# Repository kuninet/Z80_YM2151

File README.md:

# Z80マイコン FM音源(YM2151)ボード (KZ80-YM2151)

- SBC8080バスにつながるFM音源ボード KZ80-YM2151 のデータ類です。
- 詳しい説明は以下のwikiを参照してください。
  - https://github.com/kuninet/Z80_YM2151/wiki

## 回路図

[PDF版の回路図はこちら](img/YM2151.pdf)

## 部品表

- 部品表は以下にあります。
  - [https://github.com/kuninet/Z80_YM2151/blob/master/KiCAD/YM2151.ods](https://github.com/kuninet/Z80_YM2151/blob/master/KiCAD/YM2151.ods)

## 演奏プログラム&サンプルデータ

- Z80用演奏プログラムとサンプルデータはsample_musicディレクトリにあります。
  - サンプル音楽は参考リンクの音楽データをもとに作成させていただきました。
- 起動方法
  1. sample_music/hexFilesの以下のインテルHex形式ファイルを機械語モニタ等でロード
      - KZ80_YM2151.hex  (8100h番地〜)
      - sample_m.hex    (9000h番地〜)
  2. 8100番地から実行してください。

## 注意点

- 接続方法が複数あり、ジャンパ設定が複雑です。[wiki](https://github.com/kuninet/Z80_YM2151/wiki)をご覧ください。

## ライセンス

- 本リポジトリのデータは MIT License のもとで公開します。

## 参考リンク
- github h1romas4/arduino-vgmplayer
  - https://github.com/h1romas4/arduino-vgmplayer

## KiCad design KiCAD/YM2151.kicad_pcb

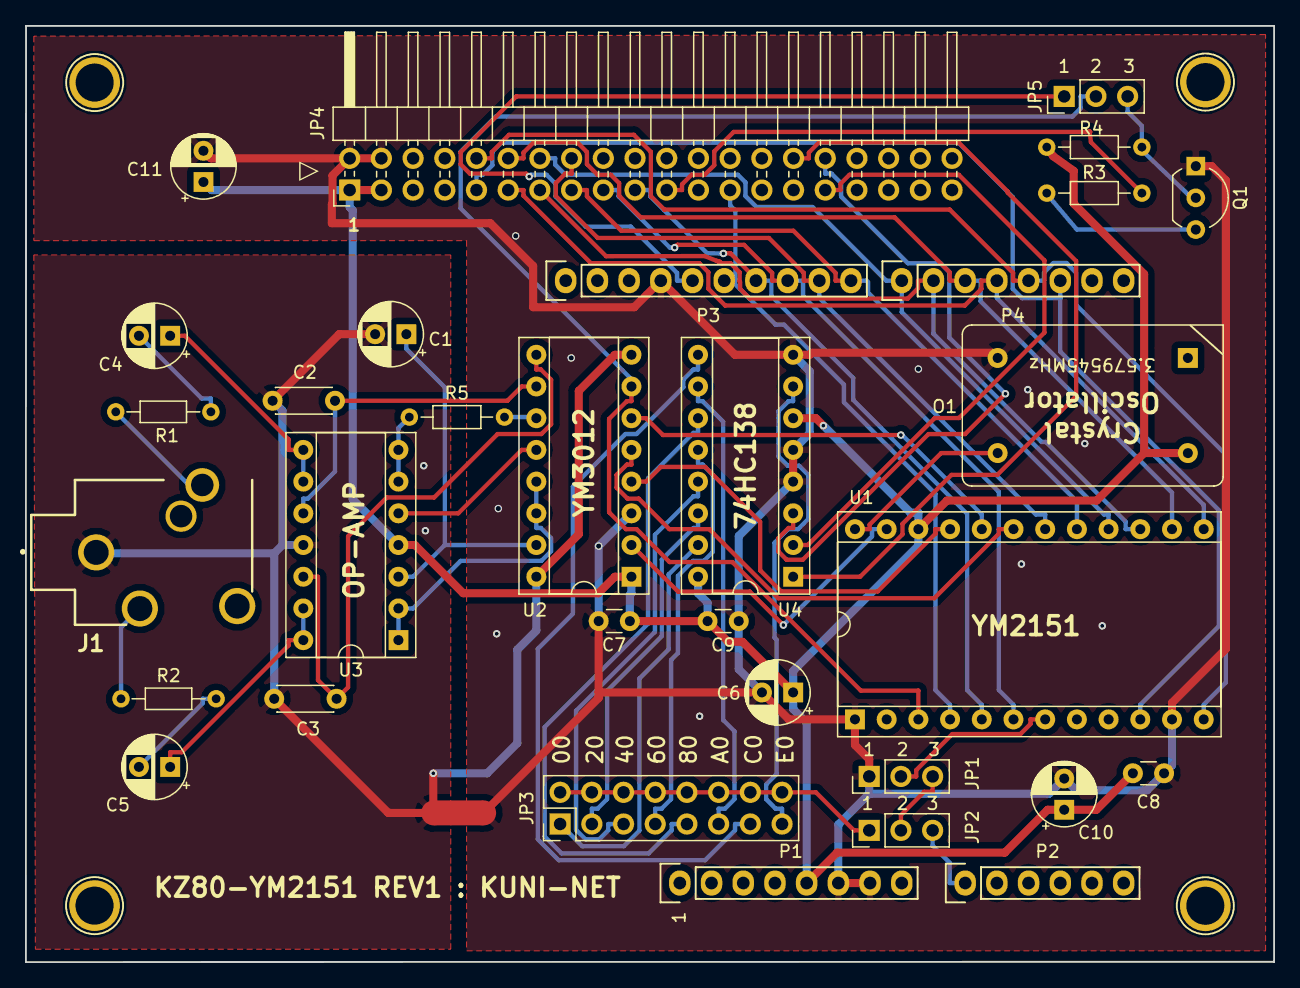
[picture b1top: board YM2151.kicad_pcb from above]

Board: 2 copper layers, 100.0 x 75.0 mm, 37 parts (0 on the bottom side), 52 nets.

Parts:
C1: 10u; CP_Radial_D5.0mm_P2.50mm
C2, C3: 3300p; C_Disc_D4.3mm_W1.9mm_P5.00mm
C4, C5, C6, C10, C11: 4.7u; CP_Radial_D5.0mm_P2.50mm
C7, C8, C9: 0.1u; C_Disc_D3.0mm_W1.6mm_P2.50mm
J1: Audio-Jack-3_2Switches; AJ-1780
JP1: Aruduino Jumper; PinHeader_1x03_P2.54mm_Vertical
JP2: SBC Jumper; PinHeader_1x03_P2.54mm_Vertical
JP3: I/O ADDR JP; PinHeader_2x08_P2.54mm_Vertical
JP4: SBC8080 BUS; PinHeader_2x20_P2.54mm_Horizontal
JP5: SBC Jumper2; PinHeader_1x03_P2.54mm_Vertical
NT1: Net-Tie_2; NetTie-2_SMD_Pad2.0mm
O1: OSCILLATOR; Oscillator_DIP-14
P1: Power; Socket_Strip_Arduino_1x08
P2: Analog; Socket_Strip_Arduino_1x06
P3: Digital; Socket_Strip_Arduino_1x10
P4: Digital; Socket_Strip_Arduino_1x08
P5, P6, P7, P8: CONN_01X01; Arduino_1pin
Q1: 2SC1815; TO-92_Inline_Wide
R1, R2, R4: 1k; R_Axial_DIN0204_L3.6mm_D1.6mm_P7.62mm_Horizontal
R3: 100k; R_Axial_DIN0204_L3.6mm_D1.6mm_P7.62mm_Horizontal
R5: 100; R_Axial_DIN0204_L3.6mm_D1.6mm_P7.62mm_Horizontal
U1: YM2151; DIP-24_W15.24mm_Socket
U2: YM3012; DIP-16_W7.62mm_Socket
U3: LMC6484; DIP-14_W7.62mm_Socket
U4: 74LS138; DIP-16_W7.62mm_Socket

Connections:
/A0: JP4.25, P3.6, U1.4
/A5: JP4.30, U4.1
/A6: JP4.31, U4.2
/A7: JP4.32, U4.3
/D0: JP4.9, P4.6, U1.10
/D1: JP4.10, P4.5, U1.12
/D2: JP4.11, P4.4, U1.13
/D3: JP4.12, P4.3, U1.14
/D4: JP4.13, P4.2, U1.15
/D5: JP4.14, P4.1, U1.16
/D6: JP4.15, P3.10, U1.17
/D7: JP4.16, P3.9, U1.18
/phM: O1.8, U1.24
/~CE: JP2.3, P2.1
/~CS: JP1.2, U1.7
/~IC: JP5.2, U1.3, U2.7
/~RD: JP4.17, P3.8, U1.6
/~WR: JP4.19, P3.7, U1.5
GNDA: C1.2, C2.2, C3.2, J1.1, NT1.1, U2.8, U2.16, U3.11
GNDD: C6.2, C7.2, C8.2, C9.2, C10.2, C11.2, JP1.1, JP4.2, JP4.4, NT1.2, O1.7, P1.6, P1.7, P3.4, Q1.1, U1.1, U1.11, U2.3, U4.4, U4.5, U4.8
unnamed: C1.1, U2.15, U3.3
unnamed: C2.1, U2.10, U3.10
unnamed: C3.1, U2.9, U3.12
unnamed: C4.1, U3.8, U3.9
unnamed: C4.2, R1.2
unnamed: C5.1, U3.13, U3.14
unnamed: C5.2, R2.2
unnamed: J1.2, R1.1
unnamed: J1.5, R2.1
unnamed: JP1.3, JP2.2
unnamed: JP2.1, JP3.2, JP3.4, JP3.6, JP3.8, JP3.10, JP3.12, JP3.14, JP3.16
unnamed: JP3.1, U4.15
unnamed: JP3.3, U4.14
unnamed: JP3.5, U4.13
unnamed: JP3.7, U4.12
unnamed: JP3.9, U4.11
unnamed: JP3.11, U4.10
unnamed: JP3.13, U4.9
unnamed: JP3.15, U4.7
unnamed: JP5.1, P3.5
unnamed: JP5.3, Q1.2, R4.1
unnamed: Q1.3, R3.1
unnamed: R5.1, U3.6, U3.7
unnamed: R5.2, U2.11
unnamed: U1.19, U2.5
unnamed: U1.20, U2.6
unnamed: U1.21, U2.4
unnamed: U1.23, U2.2
unnamed: U2.12, U3.5
unnamed: U2.13, U2.14, U3.1, U3.2
RES: JP4.21, R3.2
VCC: C6.1, C7.1, C8.1, C9.1, C10.1, C11.1, JP4.1, JP4.3, O1.14, P1.5, R4.2, U1.22, U2.1, U3.4, U4.6, U4.16

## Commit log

2018-12-13 init commit
2018-12-13 KiCADデータ・ディレクトリ移動
2018-12-13 README追加
2018-12-13 回路図イメージ等追加
2018-12-28 部品表整備
2018-12-31 README更新
2019-01-09 サンプル演奏データ/PGM 追加
2019-01-09 readme誤記修正
2019-01-10 演奏プログラム開始番地変更
2019-01-10 シルクパターン等整備
2019-01-15 クリスタル部分のシルクパターン見直し
2019-04-28 #1 演奏プログラムバグ修正 & サンブルミュージック追加
2019-04-28 サンプルミュージック 元データ修正をうけて再作成
2019-05-01 #2 演奏プログラムバグ修正 & サンブルミュージック追加
